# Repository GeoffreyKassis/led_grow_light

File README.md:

# Grow-light

USB-C PD grow light in two assemblies: an FR-4 controller (`MAIN_BOARD/`) and
a one-layer aluminum LED panel (`LED_BOARD/`), joined by an 8-wire 2×4 IDC
harness. Schematic connectivity and the as-drawn BOM come from KiCad
(`MAIN_BOARD/production/`, `LED_BOARD/production/`). This file records *why*
parts and numbers are what they are.

## Architecture

USB-C is the only power inlet. An **HUSB238** PD sink negotiates the contract
over I2C. An **STM8S003F3** requests **9 V or 12 V** (never 20 V) and PWM-dims
four **TPS61165** boost channels from `PC6`. Each channel drives one isolated
LED string: four 4000 K whites plus one 660 nm red in series.

Boost, not buck: string forward voltage is ~15.8 V, so the converter must sit
above that. TPS61165 VIN is 3–18 V recommended (20 V abs max). A 20 V PDO
leaves no boost headroom and violates that VIN rating.

On/off and dimming are MCU functions. There is no panel switch or pot.

## LED current and power

TPS61165 FB is **200 mV**. String current is set only by the sense resistor:

```
I_LED = V_FB / R_sense
      = 0.200 V / 0.82 Ω
      ≈ 0.244 A
```

A 1 Ω 1206 Basic (`C17928`) is a same-footprint swap: **0.200 A**. Dissipation
in the sense resistor is `I²R` ≈ 49 mW at 0.244 A, so 1206 is thermal margin,
not a requirement.

Nominal string voltage and power (generic 3 V whites / ~3 V red):

```
V_string ≈ 4 × 3.2 V + 3.0 V = 15.8 V
P_string ≈ 15.8 V × 0.244 A  ≈ 3.85 W
P_LEDs   ≈ 4 × 3.85 W        ≈ 15.4 W
```

XP-E2 / Oslon reds are ~2.0–2.1 V, which drops `V_string` a volt or so; the
boost still works. Input current is about **1.7 A at 9 V** or **1.3 A at 12 V**
plus converter and LDO overhead. Product class is still ~20 W at the USB-C
port.

Open-string OVP on TPS61165 is ~38 V. Do not hot-plug the LED harness with
drivers enabled.

## Controller choices

| Role | Part | Why |
|---|---|---|
| PD sink | HUSB238 `C7471904` (DFN-10 3×3) | I2C so firmware picks 9/12 V. CH224K is also Extended and has no I2C. |
| MCU | STM8S003F3P6TR `C52717` | Preferred (no $3 feeder). I2C + TIM1 PWM on remapped `PC6` (set OPT2 AFR0). |
| LED drivers | TPS61165**DRVR** `C122568` ×4 | WSON-6-EP 2×2. Do not pick the SOT-23 `C58756`. VIN 3–18 V, Vout to 38 V. |
| Inductors | CENKER CKCS4030 22 µH `C354592` | 1.0 A Irms / 1.3 A sat. Peak ~0.5 A at 9 V VIN, ~0.83 A at 5 V. No Basic 1 A 4×4. |
| Sense | 820 mΩ 1206 `C2907361` | Sets 0.244 A. True Extended; only same-footprint Basic swap is 1 Ω `C17928`. |
| Freewheel | B5819WS SOD-323 `C7420331` | 40 V / 1 A. Preferred, not a $3 line. |
| Load switch | AO3401A + BZX84C10 + 10 Ω | HUSB238 GATE after contract. 10 V VGS clamp; AO3401A is ±12 V. |
| 3.3 V | HT7533-1 | From switched VIN, 100 mA. Fine at 9/12 V; watch dissipation `(VIN−3.3)×I`. |
| USB-C | 16P `C2927039` | Cheap Extended 7.35 mm. Listing is 3 A / **5 V**; 9–12 V PD is common use but the listing is the weak one. `C165948` is 20 V / 5 A, still Extended. |
| CC ESD | USBLC6-2SC6 `C7519` | CC1/CC2 only. True Extended; no Basic SOT-23-6 equivalent. Do not tie pin 5 to 12 V. |
| Input protect | F1 3 A / 24 V PTC `C7500481`; D9 SMAJ15A | PTC is true Extended. SMAJ15A high-current clamp is ~24.4 V vs TPS61165 20 V abs max — a known gap, not a precise 15 V wall. |

HUSB238 **R2** 49.9 kΩ / **R3** 5.1 kΩ are the typical-app VSET/ISET pair.
5.1 kΩ ISET is about 1.5 A. 49.9 kΩ is **not** a datasheet VSET tap; firmware
must request 9/12 V so the default contract cannot land on 20 V.

TPS61165 VIN ceramics are 25 V. That is correct for 9/12 V and is not a 20 V
design.

## JLCPCB assembly (controller)

Economic PCBA charges **$3 per unique true Extended line**. Preferred parts
often show as “Extended” in the cart and **do not** get that fee.

**No $3 (Preferred):** D1–D4 B5819WS, D8 BZX84C10, D9 SMAJ15A, R2 49.9 kΩ, U2 STM8.

**$3 each (true Extended):** U1 HUSB238, TPS61165DRVR (one fee for four),
L1–L4 (one fee), J2 USB-C, F1 PTC, U3 USBLC6, R4–R7 820 mΩ.

Leave **J1, J3, J4** unselected and solder the TH headers yourself (avoids
the hand-solder surcharge). The only cart swap that drops a $3 line without
touching copper is **R4–R7 → `C17928` 1 Ω**.

## LED panel

Intent is a **1-layer aluminum** MCPCB: SMT on the copper face, no vias, no
through-hole parts (leads can short to the aluminum). The saved KiCad board
is already electrically single-layer (all F.Cu, no B.Cu copper, no vias) but
still declares two copper layers. Set copper layers to **1** before Gerbers
and order aluminum / 1 layer (typically 1.6 mm, 1 oz, white mask).

The checked-in `LED_BOARD/production/grow-light-LEDS.zip` is deliberately
plotted as a **front-copper-only** fabrication package. Do not regenerate it
with KiCad's automatic layer selection while the source board still declares
two copper layers, or an empty `B_Cu` file will be added and the upload may be
treated as a two-layer board.

Do **not** JLC-assemble this panel. Fab bare aluminum; populate by hand
(preheat / hot plate — the core sinks iron heat).

### Heatsink and camera mount

Selected heatsink: **Advanced Thermal Solutions
`ATS-CPX070070025-136-C1-R0`**. It is a 70 × 70 × 25 mm blue-anodized,
coarse-pitch X-cut aluminum heatsink. ATS specifies **2.17 °C/W at 100 LFM**
(~0.5 m/s) airflow; it does not publish a natural-convection value. The LED
panel is expected to put about **10–12 W of heat** into the MCPCB (15.4 W
electrical LED input less emitted light). Thus this heatsink is suitable with
intentional airflow, but is not a qualified passive full-brightness solution.
For a passive revision, target a heatsink rated **≤2.0 °C/W natural
convection** (≤1.5 °C/W preferred for a warm grow enclosure).

The ATS part has a four-corner **63.0 × 63.0 mm** mounting pattern. Direct
MCPCB mounting uses four **3.2 mm NPTH** clearance holes on that grid (centres
3.5 mm from the edges of a 70 mm square), M3 screws, and a thin layer of
thermal grease/TIM against the flat heatsink base. These are mechanical holes,
not component leads: keep front copper clear and insulate the LED-side screw
heads from copper/exposed core with shoulder washers. The current board has no
mounting holes; add them through the KiCad workflow before relying on this
mounting method.

The **1/4-20 UNC camera interface** belongs on a separate metal crossbar or
saddle bolted to the ATS factory holes, not in the heatsink or MCPCB. Capture
a steel 1/4-20 coupling nut in that crossbar for adequate thread engagement;
include an anti-rotation feature and a separate safety tether for overhead use.

This layout: **16× 3030 2-pad** whites (asymmetric A/K) and **4× 3535-3P**
reds (A/K + isolated thermal; pad 3 is unnetted). A 3030 *outline* is not a
3030 *footprint*.

### Whites

Drive ~0.244 A needs a **3 V, ~350–400 mA** 3030. Not mid-power 65 mA parts.

| MPN | Use |
|---|---|
| Cree `JK3030AWT-P-U40EA0000-N0000001` (`C17398997`) | 90 CRI, ~126 lm @ 350 mA. On the LCSC leftover list. |
| Cree `JK3030AWT-P-H40EA0000-N0000001` | Same 3 V / 400 mA max, **80 CRI**, ~154 lm @ 350 mA (~22% more light). Better for plants. |
| Everlight `XI3030P/KKE-5M4014034Z35/2N` | Still manufactured. 4000 K, 80 CRI, 3.05 V, 145 lm @ 350 mA, **max 350 mA**. 3.24×3.00 mm; check pads. |

**Cree JK3030 3 V P class is EOL** (PCN-06128, last-time buy 2026-09-04).
Remaining Digi-Key/Mouser reels are leftover. Cree’s named substitute is
`JB3030SWT-J-H40EA0000-NZ000001` (JB3030S 3 V J class): 65 mA test / 480 mA
max, **757 / Samsung-style pads**, not a 1:1 clone of JK3030 P.

Do not buy 6 V Cree `…EB…` 3030s (Vf ~6.1 V; four of those plus a red blow
the string budget and the 244 mA drive). Do not use Samsung LM301H / EVO
(EOL, and typically max ~200 mA).

### Reds

| MPN | Use |
|---|---|
| Silverlight `M3535N1IRG6U12-660NM` (`C2833507`) | Generic 3535 on LCSC. Weak horticulture part. |
| Cree XP-E2 Photo Red `XPEBPR-L1-0000-00D01` | **Still active.** 660 nm, 3.45 mm, ~2.05 V, 350 mA test / 1 A max. Closest 3535-class upgrade; confirm A/K vs the open thermal pad. |
| ams OSRAM `GH CSSRM6.24-VAA3-1-1-700-R33` | Best 660 nm (~4 µmol/J class). **3.0×3.0 mm ceramic + ~2.2 mm dome, 3-pad (A/K/thermal).** Will not solder to the 2-pad white 3030 or the 3535-3P. |

Samsung LH351H 660 nm is EOL (same lighting-LED shutdown: last ship 2025-12-31).

### Next revision — one footprint

To actually share lands, put the whole panel on **Oslon Square** (ceramic
3-pad 3.0 mm): red `GH CSSRM6.24` + white `GW CSSRM4.HW`. Same stencil,
same pad. Those whites are ~700 mA class and ~$1.50; at 0.244 A they run
cool but you pay 1 W prices. Do not mix Oslon Square pads with
Cree/Everlight 2-pad 3030 whites.

## Firmware notes

- Remap STM8 **OPT2 AFR0** so TIM1_CH1 appears on `PC6`. Default pinout does
  not.
- Hold CTRL low through reset and PD negotiation. Read the contract before
  enabling PWM.
- ~20 kHz PWM is a reasonable starting point; confirm startup does not enter
  TPS61165 EasyScale.
- Four channels at once, on the intended heatsink, after thermal equilibrium.

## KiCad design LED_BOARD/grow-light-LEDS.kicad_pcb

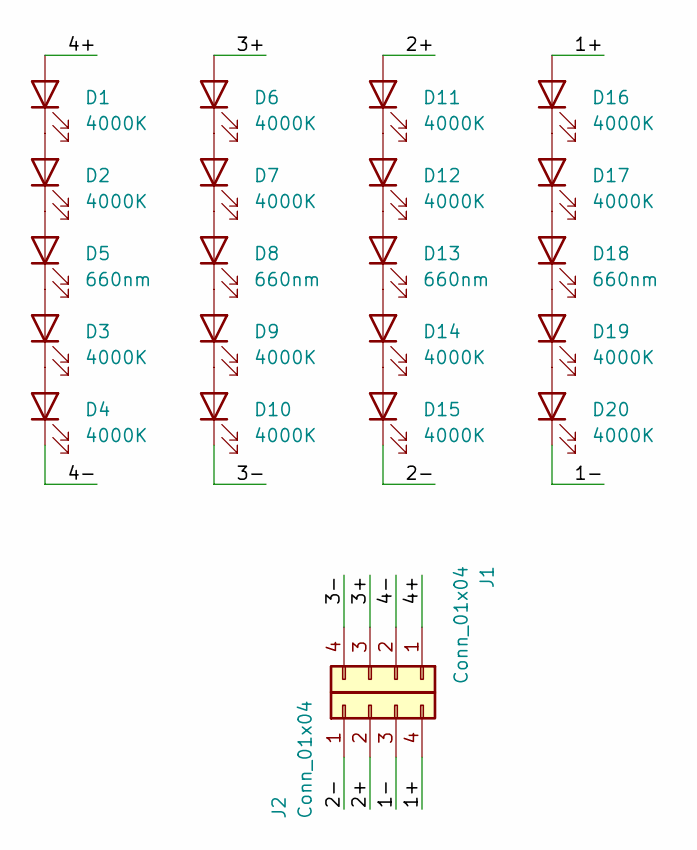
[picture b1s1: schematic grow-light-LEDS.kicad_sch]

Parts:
D1, D2, D3, D4, D6, D7, D9, D10, D11, D12, D14, D15, D16, D17, D19, D20: 4000K; LED-SMD_L3.0-W3.0-RD-1; LCSC C17398997
D5, D8, D13, D18: 660nm; LED-SMD_3P-L3.5-W3.5-RD-C; LCSC C2833507
J1, J2: Conn_01x04; FLIPPED_PRPC004SBCN-M71RC; MPN PRPC004SBCN-M71RC

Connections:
/1+: D16.2 (A), J2.4
/1-: D20.1 (K), J2.3
/2+: D11.2 (A), J2.2
/2-: D15.1 (K), J2.1
/3+: D6.2 (A), J1.3
/3-: D10.1 (K), J1.4
/4+: D1.2 (A), J1.1
/4-: D4.1 (K), J1.2
unnamed: D1.1 (K), D2.2 (A)
unnamed: D2.1 (K), D5.2 (A)
unnamed: D3.2 (A), D5.1 (K)
unnamed: D3.1 (K), D4.2 (A)
unnamed: D6.1 (K), D7.2 (A)
unnamed: D7.1 (K), D8.2 (A)
unnamed: D8.1 (K), D9.2 (A)
unnamed: D9.1 (K), D10.2 (A)
unnamed: D11.1 (K), D12.2 (A)
unnamed: D12.1 (K), D13.2 (A)
unnamed: D13.1 (K), D14.2 (A)
unnamed: D14.1 (K), D15.2 (A)
unnamed: D16.1 (K), D17.2 (A)
unnamed: D17.1 (K), D18.2 (A)
unnamed: D18.1 (K), D19.2 (A)
unnamed: D19.1 (K), D20.2 (A)

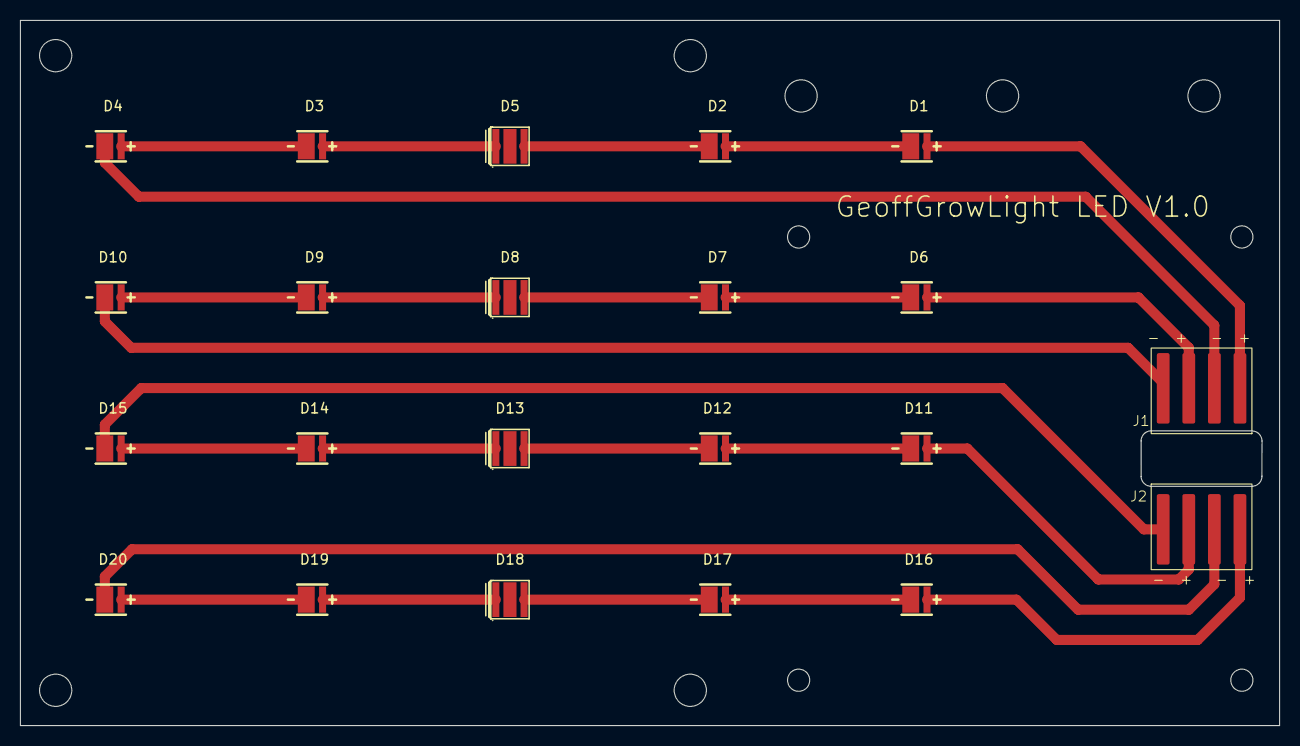
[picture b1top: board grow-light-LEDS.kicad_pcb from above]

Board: 2 copper layers, 125.0 x 70.0 mm, 22 parts (0 on the bottom side), 24 nets.

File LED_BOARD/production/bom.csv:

Designator,Footprint,Quantity,Value,LCSC Part #
"D1, D10, D11, D12, D14, D15, D16, D17, D19, D2, D20, D3, D4, D6, D7, D9",LED-SMD_L3.0-W3.0-RD-1,16,4000K,C17398997
"D13, D18, D5, D8",LED-SMD_3P-L3.5-W3.5-RD-C,4,660nm,C2833507
"J1, J2",FLIPPED_PRPC004SBCN-M71RC,2,Conn_01x04,PRPC004SBCN-M71RC

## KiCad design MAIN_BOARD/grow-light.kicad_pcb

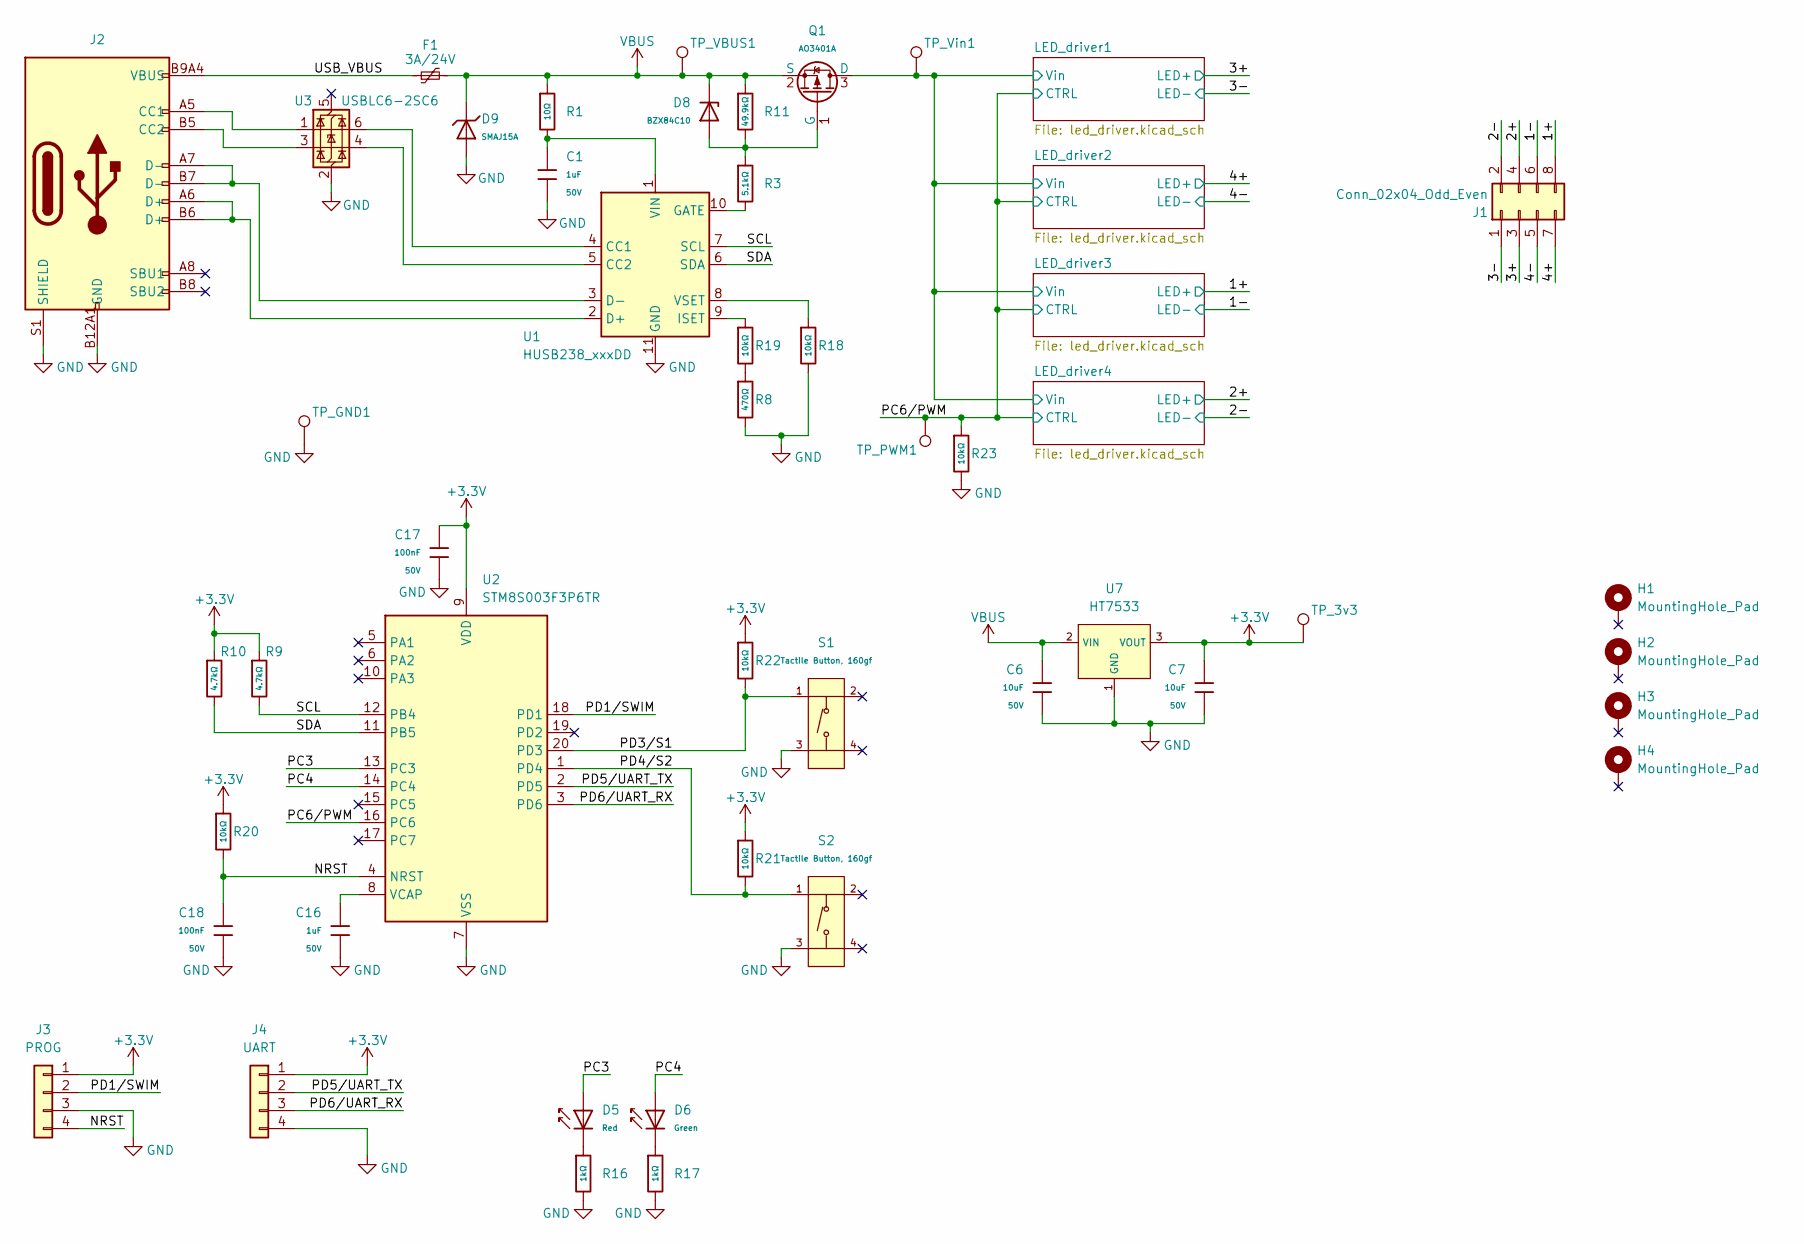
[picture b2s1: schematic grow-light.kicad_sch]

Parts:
C1, C16: 1uF; C_0603; Voltage Rated 50V; Tolerance ±10%; Part CL10A105KB8NNNC; LCSC C15849
C6, C7: 10uF; C_1206; Voltage Rated 50V; Tolerance ±10%; Part CL31A106KBHNNNE; LCSC C13585
C17, C18: 100nF; C_0603; Voltage Rated 50V; Tolerance ±10%; Part CC0603KRX7R9BB104; LCSC C14663
D5: Red; D_0805; Forward Voltage (VF) 1.6V~2.6V; Part NCD0805R1; LCSC C84256
D6: Green; D_0805; Part KT-0805G; LCSC C2297
D8: BZX84C10; D_SOT-23; Part BZX84C10; LCSC C19077470
D9: SMAJ15A; D_SMA; Part SMAJ15A; LCSC C19077535
F1: 3A/24V; Fuse_1812_4532Metric; LCSC C7500481
H1, H2, H3, H4: MountingHole_Pad; MountingHole_2.2mm_M2_Pad_Via
J1: Conn_02x04_Odd_Even; PinHeader_2x04_P2.54mm_Vertical
J2: Connector, USB-TYPE-C-16P; TYPE-C-SMD_HX-TYPE-C-16PIN; LCSC C2927039
J3: PROG; PinHeader_1x04_P2.54mm_Vertical
J4: UART; PinHeader_1x04_P2.54mm_Vertical
Q1: AO3401A; Q_SOT-23; Part AO3401A; LCSC C15127
R1: 10Ω; R_0805; Overload Voltage (Max) 150V; Tolerance ±1%; Part 0805W8F100JT5E; LCSC C17415
R3: 5.1kΩ; R_0805; Overload Voltage (Max) 150V; Tolerance ±1%; Part 0805W8F5101T5E; LCSC C27834
R8: 470Ω; R_0603; Overload Voltage (Max) 75V; Tolerance ±1%; Part 0603WAF4700T5E; LCSC C23179
R9, R10: 4.7kΩ; R_0603; Overload Voltage (Max) 75V; Tolerance ±1%; Part 0603WAF4701T5E; LCSC C23162
R11: 49.9kΩ; R_0603; Overload Voltage (Max) 75V; Tolerance ±1%; Part 0603WAF4992T5E; LCSC C23184
R16, R17: 1kΩ; R_0603; Overload Voltage (Max) 75V; Tolerance ±1%; Part 0603WAF1001T5E; LCSC C21190
R18, R19, R20, R21, R22, R23: 10kΩ; R_0603; Overload Voltage (Max) 75V; Tolerance ±1%; Part 0603WAF1002T5E; LCSC C25804
S1, S2: Tactile Button, 160gf; SW-SMD_4P-L5.1-W5.1-P3.70-LS6.5-TL-2; Voltage Rating (Dc) 12V; Part TS-1187A-B-A-B; LCSC C318884
TP_3v3: TestPoint; PinHeader_1x01_P1.00mm_Vertical
TP_GND1: TestPoint; PinHeader_1x01_P1.00mm_Vertical
TP_PWM1: TestPoint; PinHeader_1x01_P1.00mm_Vertical
TP_VBUS1: TestPoint; PinHeader_1x01_P1.00mm_Vertical
TP_Vin1: TestPoint; PinHeader_1x01_P1.00mm_Vertical
U1: HUSB238_xxxDD; WDFN-10-1EP_3x3mm_P0.5mm_EP1.8x2.5mm; LCSC C7471904
U2: STM8S003F3P6TR; TSSOP-20_4.4x6.5mm_P0.65mm; Operating Voltage Range 2.95V~5.5V; Low Voltage Detection T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 2.95V~5.5V; Part STM8S003F3P6TR; LCSC C52717
U3: USBLC6-2SC6; SOT-23-6; LCSC C7519
U7: HT7533; SOT-89-3_L4.5-W2.5-P1.50-LS4.2-BR; Output Voltage 3.3V; Dropout Voltage 55mV@(1mA); Part HT7533-1; LCSC C14289

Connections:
+3.3V: C7.1, C17.1, J3.1, J4.1, R9.1, R10.1, R20.1, R21.1, R22.1, TP_3v3.1 (1_1), U2.9 (VDD), U7.3 (VOUT)
/1+: J1.8; also elsewhere on the board
/1-: J1.6; also elsewhere on the board
/2+: J1.4; also elsewhere on the board
/2-: J1.2; also elsewhere on the board
/3+: J1.3; also elsewhere on the board
/3-: J1.1; also elsewhere on the board
/4+: J1.7; also elsewhere on the board
/4-: J1.5; also elsewhere on the board
/LED_driver1/Vin: Q1.3 (D), TP_Vin1.1 (1_1); also elsewhere on the board
/NRST: C18.1, J3.4, R20.2, U2.4 (NRST)
/PC3: D5.2, U2.13 (PC3)
/PC4: D6.2, U2.14 (PC4)
/PC6/PWM: R23.1, TP_PWM1.1 (1_1), U2.16 (PC6); also elsewhere on the board
/PD1/SWIM: J3.2, U2.18 (PD1)
/PD3/S1: R22.2, S1.1 (A), U2.20 (PD3)
/PD4/S2: R21.2, S2.1 (A), U2.1 (PD4)
/PD5/UART_TX: J4.2, U2.2 (PD5)
/PD6/UART_RX: J4.3, U2.3 (PD6)
/SCL: R9.2, U1.7 (SCL), U2.12 (PB4)
/SDA: R10.2, U1.6 (SDA), U2.11 (PB5)
/USB_VBUS: F1.1, J2.A9B4 (VBUS), J2.B9A4 (VBUS)
GND: C1.2, C6.2, C7.2, C16.2, C17.2, C18.2, D9.2, J2.A12B1 (GND), J2.B12A1 (GND), J2.S1 (SHIELD), J3.3, J4.4, R8.2, R16.2, R17.2, R18.2, R23.2, S1.3 (C), S2.3 (C), TP_GND1.1 (1_1), U1.11 (GND), U2.7 (VSS), U3.2 (GND), U7.1 (GND); also elsewhere on the board
unnamed: D5.1, R16.1
unnamed: D6.1, R17.1
unnamed: J2.A5 (CC1), U3.1 (I/O1)
unnamed: J2.B5 (CC2), U3.3 (I/O2)
unnamed: D8.1, Q1.1 (G), R3.1, R11.2
unnamed: R8.1, R19.2
unnamed: U1.4 (CC1), U3.6 (I/O1)
unnamed: U1.5 (CC2), U3.4 (I/O2)
unnamed: J2.A6 (D+), J2.B6 (D+), U1.2 (D+)
unnamed: J2.A7 (D-), J2.B7 (D-), U1.3 (D-)
unnamed: R3.2, U1.10 (GATE)
unnamed: R19.1, U1.9 (ISET)
unnamed: C1.1, R1.2, U1.1 (VIN)
unnamed: R18.1, U1.8 (VSET)
unnamed: C16.1, U2.8 (VCAP)
VBUS: C6.1, D8.3, D9.1, F1.2, Q1.2 (S), R1.1, R11.1, TP_VBUS1.1 (1_1), U7.2 (VIN)

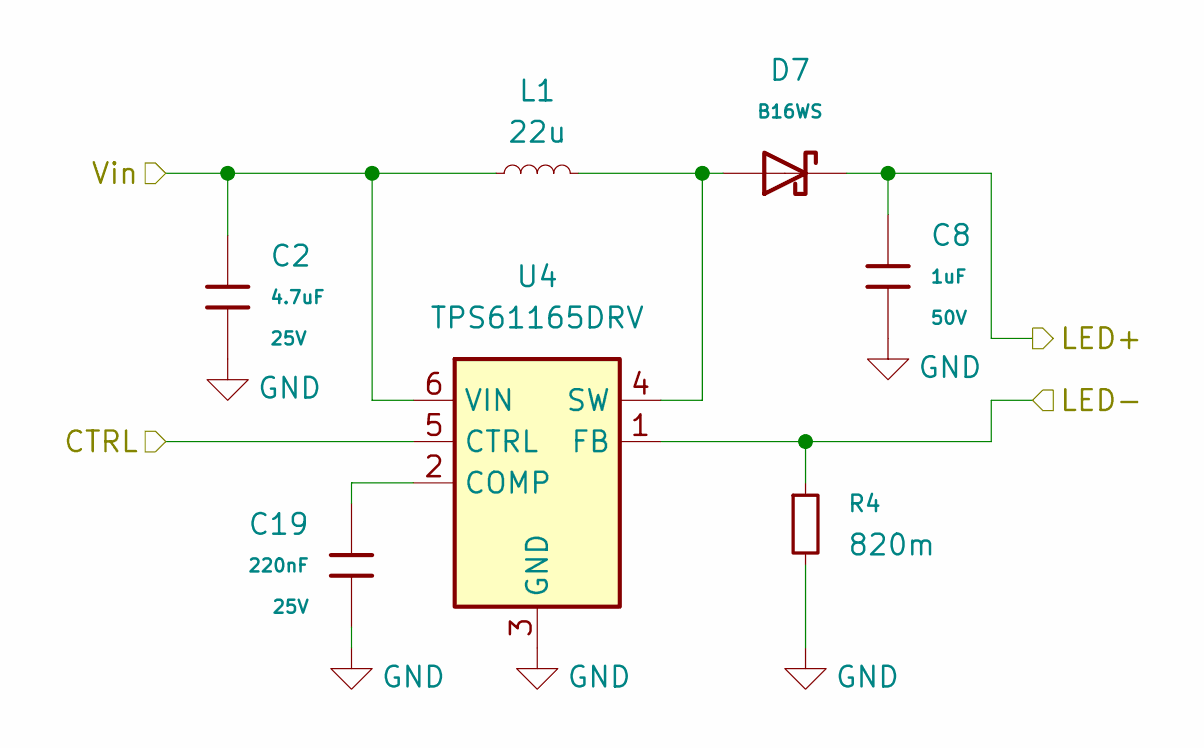
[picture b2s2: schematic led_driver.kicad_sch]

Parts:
C2: 4.7uF; C_0805; Voltage Rated 25V; Tolerance ±10%; Part CL21A475KAQNNNE; LCSC C1779
C8: 1uF; C_0603; Voltage Rated 50V; Tolerance ±10%; Part CL10A105KB8NNNC; LCSC C15849
C19: 220nF; C_0603; Voltage Rated 25V; Tolerance ±10%; Part CL10B224KA8NNNC; LCSC C21120
D7: B16WS; D_SOD-323; Forward Voltage (Vf@If) 0.7V@1.0A; Reverse Voltage (Vr) 60V; Part B16WS; LCSC C7420327
L1: 22u; L_Cenker_CKCS4030; LCSC C354592
R4: 820m; R_1206_3216Metric; LCSC C2907361
U4: TPS61165DRV; WSON-6-1EP_2x2mm_P0.65mm_EP1x1.6mm; LCSC C122568

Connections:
/3+: C8.1, D7.1; also elsewhere on the board
/3-: R4.1, U4.1 (FB); also elsewhere on the board
/LED_driver1/Vin: C2.1, L1.1, U4.6 (VIN); also elsewhere on the board
/PC6/PWM: U4.5 (CTRL); also elsewhere on the board
GND: C2.2, C8.2, C19.2, R4.2, U4.3 (GND), U4.7 (GND); also elsewhere on the board
unnamed: C19.1, U4.2 (COMP)
unnamed: D7.2, L1.2, U4.4 (SW)

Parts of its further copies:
C3, C4, C5: 4.7uF; C_0805; Voltage Rated 25V; Tolerance ±10%; Part CL21A475KAQNNNE; LCSC C1779
C9, C10, C11: 1uF; C_0603; Voltage Rated 50V; Tolerance ±10%; Part CL10A105KB8NNNC; LCSC C15849
C20, C21, C22: 220nF; C_0603; Voltage Rated 25V; Tolerance ±10%; Part CL10B224KA8NNNC; LCSC C21120
D10, D11, D12: B16WS; D_SOD-323; Forward Voltage (Vf@If) 0.7V@1.0A; Reverse Voltage (Vr) 60V; Part B16WS; LCSC C7420327
L2, L3, L4: 22u; L_Cenker_CKCS4030; LCSC C354592
R5, R6, R7: 820m; R_1206_3216Metric; LCSC C2907361
U5, U11, U12: TPS61165DRV; WSON-6-1EP_2x2mm_P0.65mm_EP1x1.6mm; LCSC C122568

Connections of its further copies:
/1+: C10.1, D11.1; also elsewhere on the board
/1-: R6.1, U11.1 (FB); also elsewhere on the board
/2+: C11.1, D12.1; also elsewhere on the board
/2-: R7.1, U12.1 (FB); also elsewhere on the board
/4+: C9.1, D10.1; also elsewhere on the board
/4-: R5.1, U5.1 (FB); also elsewhere on the board
/LED_driver1/Vin: C3.1, C4.1, C5.1, L2.1, L3.1, L4.1, U5.6 (VIN), U11.6 (VIN), U12.6 (VIN); also elsewhere on the board
/PC6/PWM: U5.5 (CTRL), U11.5 (CTRL), U12.5 (CTRL); also elsewhere on the board
GND: C3.2, C4.2, C5.2, C9.2, C10.2, C11.2, C20.2, C21.2, C22.2, R5.2, R6.2, R7.2, U5.3 (GND), U5.7 (GND), U11.3 (GND), U11.7 (GND), U12.3 (GND), U12.7 (GND); also elsewhere on the board
unnamed: C20.1, U5.2 (COMP)
unnamed: D10.2, L2.2, U5.4 (SW)
unnamed: C21.1, U11.2 (COMP)
unnamed: D11.2, L3.2, U11.4 (SW)
unnamed: C22.1, U12.2 (COMP)
unnamed: D12.2, L4.2, U12.4 (SW)

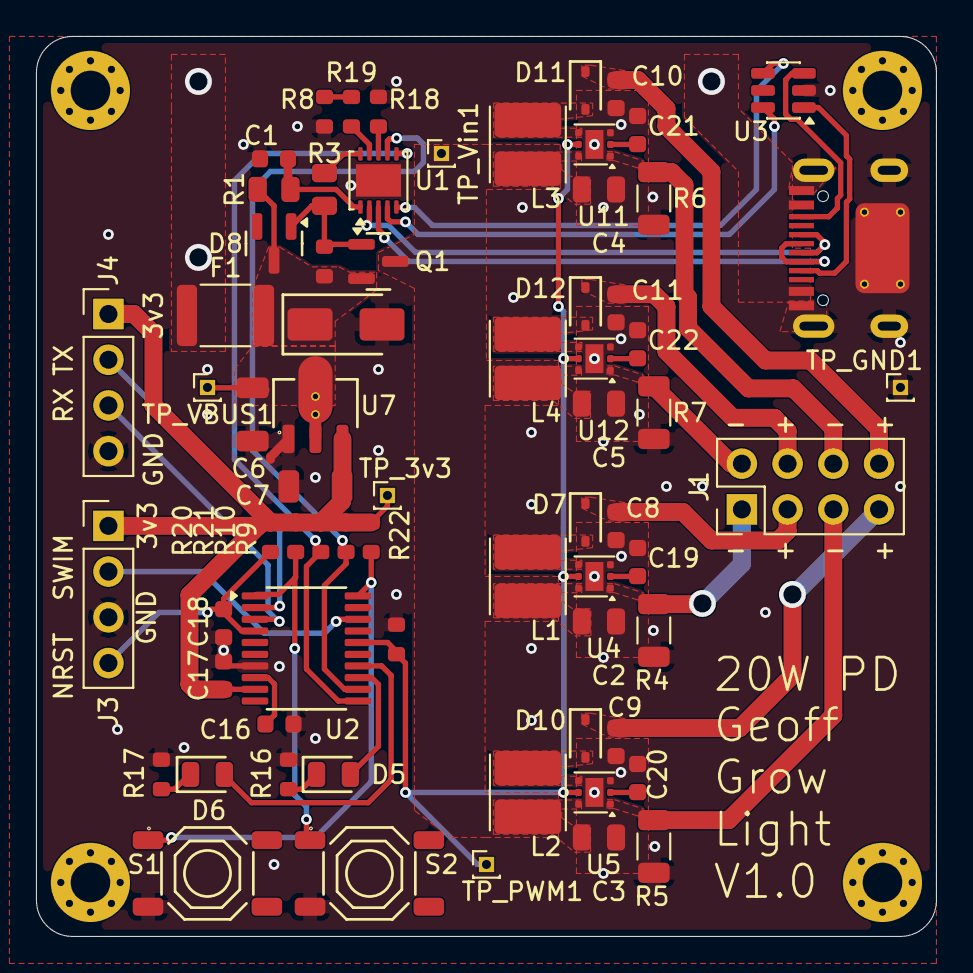
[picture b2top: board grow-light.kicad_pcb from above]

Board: 4 copper layers, 50.0 x 50.0 mm, 73 parts (0 on the bottom side), 47 nets.

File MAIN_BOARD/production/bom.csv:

Designator,Footprint,Quantity,Value,LCSC Part #
"C1, C10, C11, C16, C8, C9",C_0603,6,1uF,C15849
"C17, C18",C_0603,2,100nF,C14663
"C19, C20, C21, C22",C_0603,4,220nF,C21120
"C2, C3, C4, C5",C_0805,4,4.7uF,C1779
"C6, C7",C_1206,2,10uF,C13585
"D10, D11, D12, D7",D_SOD-323,4,B16WS,C7420327
D5,D_0805,1,Red,C84256
D6,D_0805,1,Green,C2297
D8,D_SOT-23,1,BZX84C10,C19077470
D9,D_SMA,1,SMAJ15A,C19077535
F1,1812,1,3A/24V,C7500481
J1,PinHeader_2x04_P2.54mm_Vertical,1,Conn_02x04_Odd_Even,
J2,TYPE-C-SMD_HX-TYPE-C-16PIN,1,"Connector, USB-TYPE-C-16P",C2927039
J3,PinHeader_1x04_P2.54mm_Vertical,1,PROG,
J4,PinHeader_1x04_P2.54mm_Vertical,1,UART,
"L1, L2, L3, L4",L_Cenker_CKCS4030,4,22u,C354592
Q1,Q_SOT-23,1,AO3401A,C15127
R1,R_0805,1,10Ω,C17415
"R10, R9",R_0603,2,4.7kΩ,C23162
R11,R_0603,1,49.9kΩ,C23184
"R16, R17",R_0603,2,1kΩ,C21190
"R18, R19, R20, R21, R22, R23",R_0603,6,10kΩ,C25804
R3,R_0805,1,5.1kΩ,C27834
"R4, R5, R6, R7",1206,4,820m,C2907361
R8,R_0603,1,470Ω,C23179
"S1, S2",SW-SMD_4P-L5.1-W5.1-P3.70-LS6.5-TL-2,2,"Tactile Button, 160gf",C318884
"TP_3V3, TP_GND1, TP_PWM1, TP_VBUS1, TP_VIN1",PinHeader_1x01_P1.00mm_Vertical,5,TestPoint,
U1,WDFN-10-1EP_3x3mm_P0.5mm_EP1.8x2.5mm,1,HUSB238_xxxDD,C7471904
"U11, U12, U4, U5",WSON-6-1EP_2x2mm_P0.65mm_EP1x1.6mm,4,TPS61165DRV,C122568
U2,TSSOP-20_4.4x6.5mm_P0.65mm,1,STM8S003F3P6TR,C52717
U3,SOT-23-6,1,USBLC6-2SC6,C7519
U7,SOT-89-3_L4.5-W2.5-P1.50-LS4.2-BR,1,HT7533,C14289
